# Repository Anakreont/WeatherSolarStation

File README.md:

# WeatherSolarStation
WeatherSolarStation
more information on my website https://sq9gol.xyz/weather-statnion/

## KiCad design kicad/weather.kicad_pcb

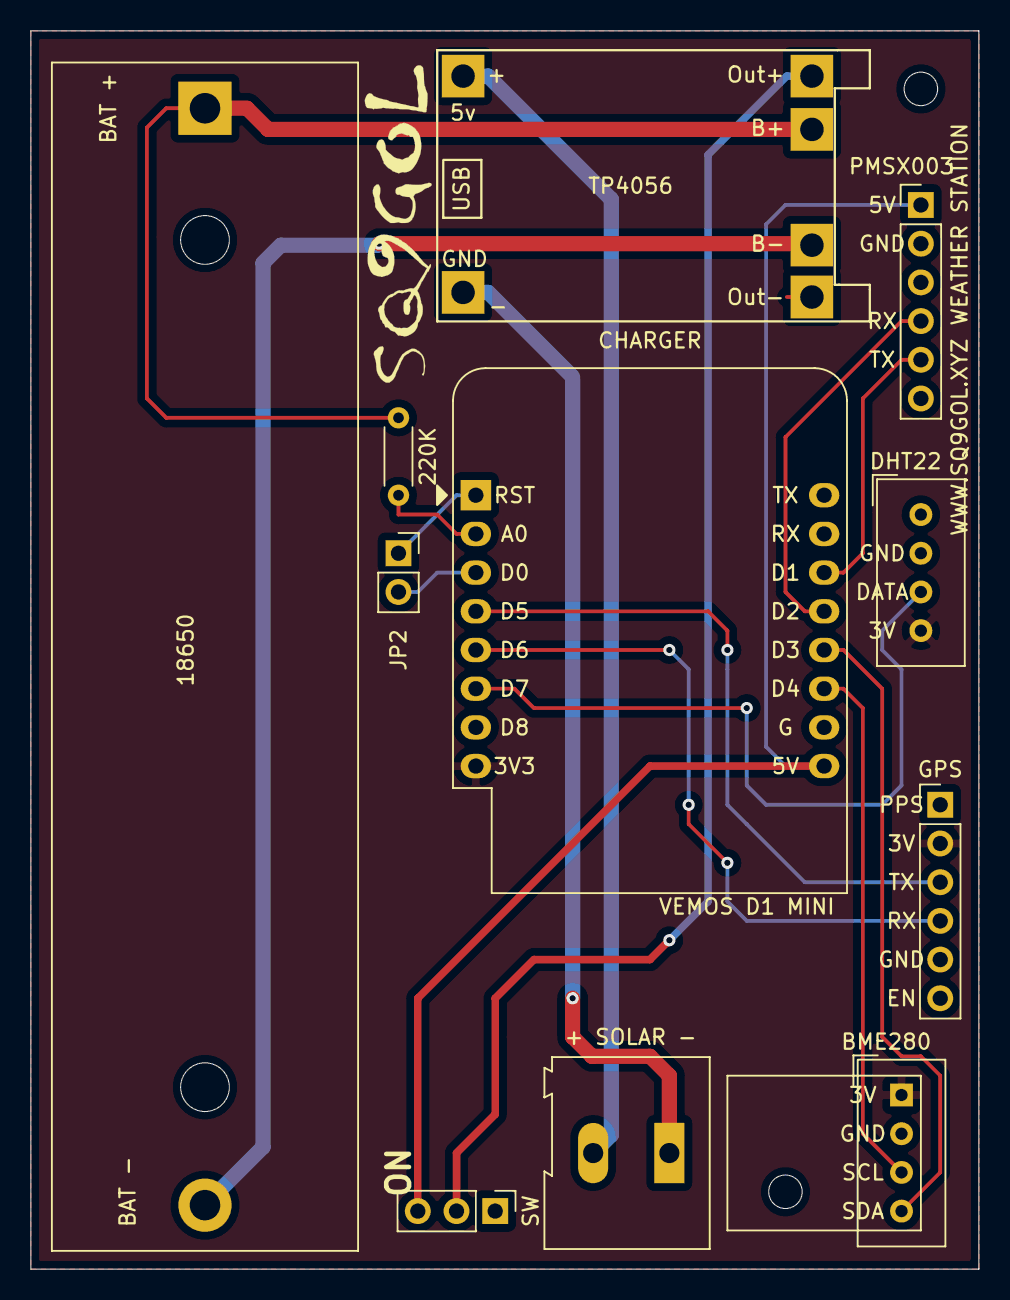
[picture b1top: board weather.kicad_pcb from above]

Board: 2 copper layers, 62.2 x 81.3 mm, 10 parts (0 on the bottom side), 2 nets.

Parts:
220K: JP2; R_Axial_DIN0204_L3.6mm_D1.6mm_P5.08mm_Horizontal
+ SOLAR -: TerminalBlock_Altech_AK300-2_P5.00mm
BAT +: BatteryHolder_MPD_BH-18650-PC2
BME280: Aosong_DHT11_5.5x12.0_P2.54mm
CHARGER: TP4056-18650
DHT22: Aosong_DHT11_5.5x12.0_P2.54mm
GPS: PinHeader_1x06_P2.54mm_Vertical
PMSX003: PinHeader_1x06_P2.54mm_Vertical
SW: PinHeader_1x03_P2.54mm_Vertical
VEMOS D1 MINI: WEMOS_D1_mini_light

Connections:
/3V3: BME280.1, DHT22.4, GPS.2, VEMOS D1 MINI.8
/GND: BME280.2, CHARGER.4, DHT22.2, GPS.5, PMSX003.2, VEMOS D1 MINI.10
